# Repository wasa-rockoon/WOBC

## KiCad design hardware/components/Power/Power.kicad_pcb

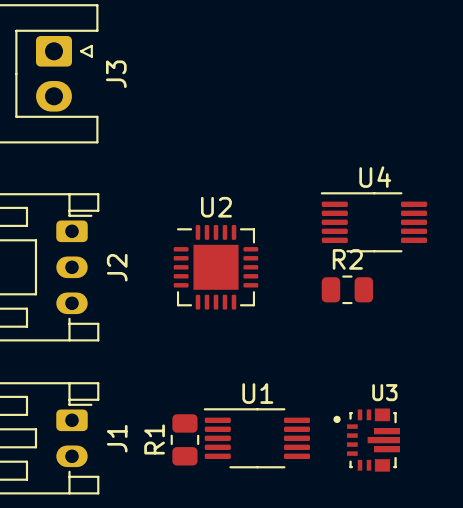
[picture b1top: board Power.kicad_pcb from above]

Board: 2 copper layers, 10 parts (1 on the bottom side), 11 nets, no tracks yet.

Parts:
BT1: Battery_Cell; BatteryHolder_Keystone_3002_1x2032
J1: LiPo; JST_PH_S2B-PH-K_1x02_P2.00mm_Horizontal
J2: Temp&Heater; JST_PH_S3B-PH-K_1x03_P2.00mm_Horizontal
J3: Battery; JST_XH_S2B-XH-A_1x02_P2.50mm_Horizontal
R1, R2: 50mΩ; R_0805_2012Metric
U1, U4: INA226; VSSOP-10_3x3mm_P0.5mm
U2: MCP73871-1CC; QFN-20-1EP_4x4mm_P0.5mm_EP2.5x2.5mm
U3: TPS63070RNMR; VREG_TPS63070RNMR

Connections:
GND: BT1.2 (-), J1.2, J2.3, J3.2, U1.7 (GND), U2.10 (V_{SS}), U2.11 (V_{SS}), U2.21 (V_{SS}), U4.7 (GND)
I2C_SCL: U1.5 (SCL), U4.5 (SCL)
I2C_SDA: U1.4 (SDA), U4.4 (SDA)
unnamed: U2.1 (OUT), U2.20 (OUT)
unnamed: J2.2, U2.5 (THERM)
unnamed: U2.18 (IN), U2.19 (IN)
unnamed: R1.1, U2.14 (V_{BAT}), U2.15 (V_{BAT}), U2.16 (V_{BAT_SENSE}), U4.6 (VS), U4.9 (Vin-)
unnamed: R1.2, U4.8 (Vbus), U4.10 (Vin+)
VBUS: U2.2 (VPCC), U2.3 (SEL)
VDD: R2.2, U1.9 (Vin-)
VDD_BUS: R2.1, U1.6 (VS), U1.8 (Vbus), U1.10 (Vin+)

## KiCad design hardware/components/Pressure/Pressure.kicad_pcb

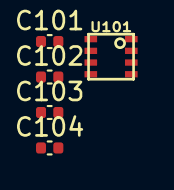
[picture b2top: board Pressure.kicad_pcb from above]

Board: 2 copper layers, 5 parts (0 on the bottom side), 2 nets, no tracks yet.

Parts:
C101, C104: 10μF; C_0402_1005Metric
C102, C103: 100nF; C_0402_1005Metric
U101: BME280

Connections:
3V3: C101.1, C102.1, C103.1, C104.1, U101.2 (CSB), U101.6 (VDDIO), U101.8 (VDD)
GND: C101.2, C102.2, C103.2, C104.2, U101.1 (GND), U101.5 (SDO), U101.7 (GND)

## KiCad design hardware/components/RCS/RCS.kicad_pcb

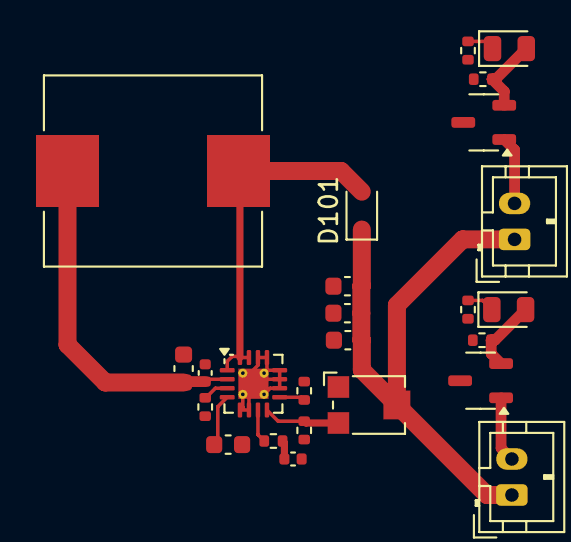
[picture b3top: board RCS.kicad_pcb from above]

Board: 2 copper layers, 25 parts (0 on the bottom side), 16 nets.

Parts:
C101: 47nF; C_0603_1608Metric
C102: 10uF; C_0603_1608Metric
C103, C104: 0.1uF; C_0402_1005Metric
C105, C106, C107: 4.7uF; C_0603_1608Metric
D101: D; D_SOD-323
D102, D103: Valve; D_0805_2012Metric
J101, J102: Conn_01x02; JST_PH_B2B-PH-K_1x02_P2.00mm_Vertical
L101: 10uH; L_Chilisin_BMRF00101040
Q101, Q102: NMOS; SOT-23-3
R101, R102, R105, R106: 100k; R_0402_1005Metric
R103: 2.2k; R_0402_1005Metric
R104, R107, R108: 1k; R_0402_1005Metric
RV101: 20k; Potentiometer_Bourns_TC33X_Vertical
U101: WQFN-16-1EP_3x3mm_P0.5mm_EP1.68x1.68mm_ThermalVias

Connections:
/RCS_EN: R101.1, U101.3 (EN)
/RCS_VIN: C102.1, C104.1, L101.1, U101.2 (VIN)
/valve1: D102.2 (A), Q101.2 (G), R105.1
/valve2: D103.2 (A), Q102.2 (G), R106.1
GND: C101.2, C102.2, C103.2, C104.2, C105.2, C106.2, C107.2, Q101.3 (S), Q102.3 (S), R101.2, R102.2, R104.2, R105.2, R106.2, R107.2, R108.2, U101.5 (SYNC), U101.6 (AGND), U101.10 (NC), U101.11 (PGND), U101.12 (PGND), U101.13 (PGND), U101.14 (NC), U101.17 (EP)
unnamed: C103.1, R103.2
unnamed: D101.2 (A), L101.2, U101.1 (SW), U101.15 (SW), U101.16 (SW)
unnamed: C105.1, C106.1, C107.1, D101.1 (K), J101.1, J102.1, RV101.2
unnamed: D102.1 (K), R107.1
unnamed: D103.1 (K), R108.1
unnamed: J101.2, Q101.1 (D)
unnamed: J102.2, Q102.1 (D)
unnamed: R103.1, U101.7 (COMP)
unnamed: R104.1, RV101.3, U101.8 (FB)
unnamed: R102.1, U101.9 (FREQ)
unnamed: C101.1, U101.4 (SS)

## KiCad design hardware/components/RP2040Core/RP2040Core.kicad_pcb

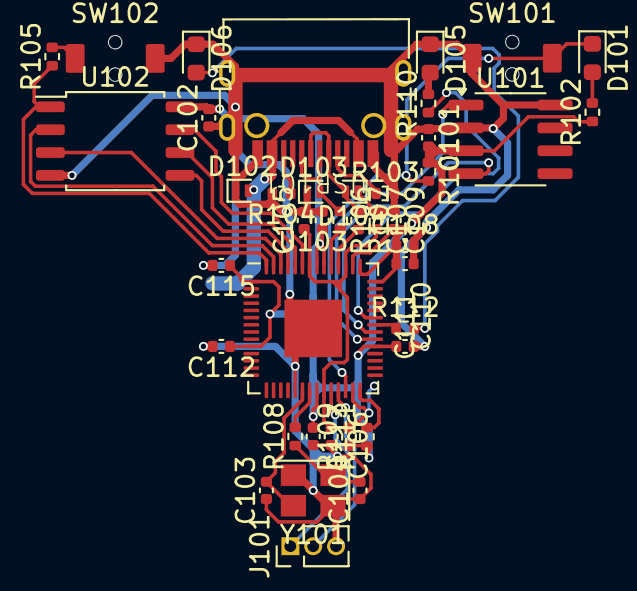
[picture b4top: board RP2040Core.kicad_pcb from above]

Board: 2 copper layers, 41 parts (0 on the bottom side), 32 nets.

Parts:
C101, C102, C105, C106, C108, C110, C111, C112, C113, C114, C115: 100nF; C_0402_1005Metric
C103, C104: 27pF; C_0402_1005Metric
C107, C109: 1uF; C_0402_1005Metric
D101: RESET; LED_0603_1608Metric
D102, D103, D104: 5V; D_SOD-882
D105: STAT; LED_0603_1608Metric
D106: ERROR; LED_0603_1608Metric
J101: DEBUG; PinHeader_1x03_P1.27mm_Vertical
R101, R109, R111: 10k; R_0402_1005Metric
R102, R105, R108, R110, R112: 1k; R_0402_1005Metric
R103, R104: 5.1k; R_0402_1005Metric
R106, R107: 22.4; R_0402_1005Metric
SW101: RESET_sw; TVAF06-A020B-R
SW102: BOOT0; TVAF06-A020B-R
U101: SN65HVD230; SOIC-8_3.9x4.9mm_P1.27mm
U102: W25Q128JVS; SOIC-8_5.23x5.23mm_P1.27mm
U103: RP2040; QFN-56-1EP_7x7mm_P0.4mm_EP3.2x3.2mm
USB101: USB_C_Receptacle_USB2.0; USB_C_TYPEC-301S-ACP16X7
Y101: Crystal_GND24; Crystal_SMD_3225-4Pin_3.2x2.5mm

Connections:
/CAN_RX: U101.4 (R), U103.35 (GPIO23)
/CAN_TX: U101.1 (D), U103.34 (GPIO22)
/I2C_SCL: R111.2, U103.28 (GPIO17)
/I2C_SDA: R109.2, U103.27 (GPIO16)
/USB_D+: D103.2 (A2), R106.1, USB101.A6 (D+), USB101.B6 (D+)
/USB_D-: D104.2 (A2), R107.1, USB101.A7 (D-), USB101.B7 (D-)
GND: C101.1, C102.1, C103.1, C104.1, C105.2, C106.2, C107.1, C108.2, C109.1, C110.2, C111.2, C112.2, C113.2, C114.2, C115.2, D102.1 (A1), D103.1 (A1), D104.1 (A1), D105.1 (K), D106.1 (K), J101.3, R103.2, R104.2, SW101.2, SW102.1, U101.2 (GND), U101.8 (Rs), U102.4 (GND), U103.19 (TESTEN), U103.57 (GND), USB101.A1 (GND), USB101.A12 (GND), USB101.B1 (GND), USB101.B12 (GND), USB101.S1 (SHIELD), Y101.2, Y101.4
unnamed: C104.2, R108.1, Y101.1
unnamed: D101.2 (A), R102.2
unnamed: D105.2 (A), R110.2
unnamed: D106.2 (A), R112.2
unnamed: J101.1, U103.24 (SWCLK)
unnamed: J101.2, U103.25 (SWD)
unnamed: R105.2, SW102.2
unnamed: U102.6 (CLK), U103.52 (QSPI_SCLK)
unnamed: U102.5 (DI(IO0)), U103.53 (QSPI_SD0)
unnamed: U102.2 (DO(IO1)), U103.55 (QSPI_SD1)
unnamed: U102.3 (IO2), U103.54 (QSPI_SD2)
unnamed: U102.7 (IO3), U103.51 (QSPI_SD3)
unnamed: R105.1, U102.1 (~CS), U103.56 (QSPI_SS)
unnamed: R112.1, U103.36 (GPIO24)
unnamed: R110.1, U103.37 (GPIO25)
unnamed: R107.2, U103.46 (USB_DM)
unnamed: R106.2, U103.47 (USB_DP)
unnamed: C105.1, C106.1, C107.2, U103.23 (DVDD), U103.45 (VREG_VOUT), U103.50 (DVDD)
unnamed: C103.2, U103.20 (XIN), Y101.3
unnamed: R108.2, U103.21 (XOUT)
unnamed: R103.1, USB101.A5 (CC1)
unnamed: R104.1, USB101.B5 (CC2)
RESET: D101.1 (K), R101.2, SW101.1, U103.26 (RUN)
VBUS: D102.2 (A2), USB101.A4 (VBUS), USB101.A9 (VBUS), USB101.B4 (VBUS), USB101.B9 (VBUS)
VDD: C101.2, C102.2, C108.1, C109.2, C110.1, C111.1, C112.1, C113.1, C114.1, C115.1, R101.1, R102.1, R109.1, R111.1, U101.3 (VCC), U102.8 (VCC), U103.1 (IOVDD), U103.10 (IOVDD), U103.22 (IOVDD), U103.33 (IOVDD), U103.42 (IOVDD), U103.43 (ADC_AVDD), U103.44 (VREG_IN), U103.48 (USB_VDD), U103.49 (IOVDD)

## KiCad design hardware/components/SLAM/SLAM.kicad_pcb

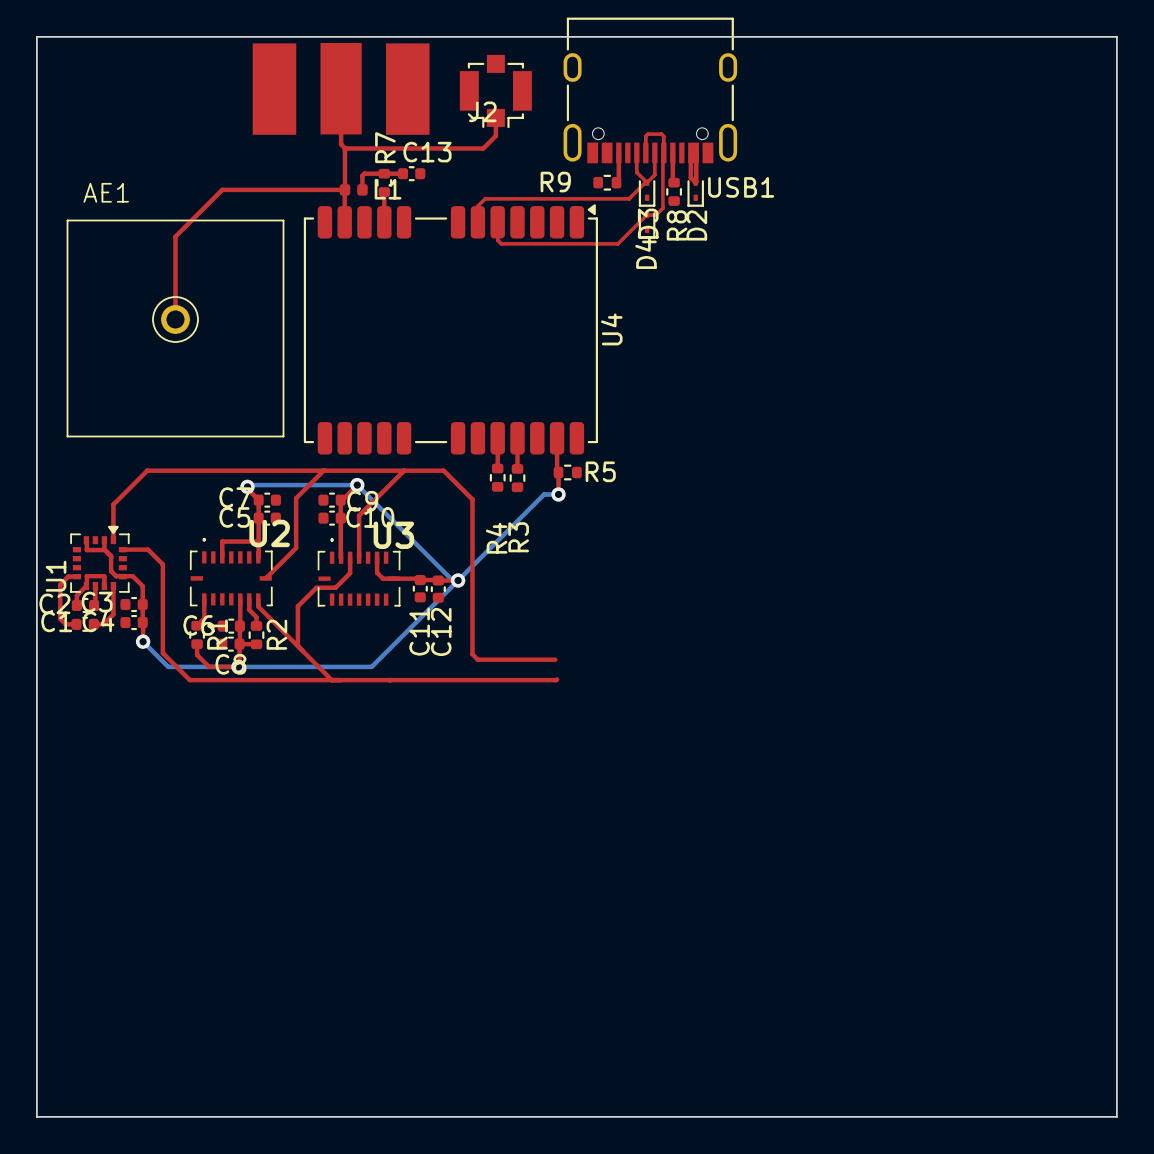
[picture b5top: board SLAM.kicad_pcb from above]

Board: 2 copper layers, 60.0 x 60.0 mm, 33 parts (0 on the bottom side), 19 nets.

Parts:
AE1: Antenna; GNSS_Antenna_1212
C1: 0.22μF; C_0402_1005Metric
C2: 4.7μF; C_0402_1005Metric
C3, C5, C6, C10, C11, C13: 100nF; C_0402_1005Metric
C4, C7, C8, C9, C12: 10μF; C_0402_1005Metric
D2, D3, D4: 5V; D_SOD-923
J1: SMA; SMA_aki
J2: U.FL; U.FL_Molex_MCRF_73412-0110_Vertical
L1: 27nH, 300mA; L_0402_1005Metric
R1, R2: 4.7K; R_0402_1005Metric
R3, R4: 33; R_0402_1005Metric
R5: 100K; R_0402_1005Metric
R7: 10; R_0402_1005Metric
R8, R9: 22k; R_0402_1005Metric
U1: LGA-16_3x3mm_P0.5mm
U2: BMI088
U3: BMI088
U4: NEO-M9N; ublox_NEO
USB1: USB_C_Receptacle_USB2.0; USB_C_Receptacle_XKB_U262-16XN-4BVC11

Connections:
3V3: C3.1, C4.1, C5.1, C6.1, C7.1, C8.1, C9.1, C10.1, C11.1, C12.1, R1.2, R2.2, R5.1, U1.2 (VDD), U1.4 (S1), U1.13 (VDDIO), U2.3 (VDD), U2.7 (PS), U2.11 (VDDIO), U3.2 (CSB), U3.6 (VDDIO), U3.8 (VDD), U4.23 (VCC)
/USB_D+: D3.2 (A2), U4.6 (USB_DP), USB1.A6 (D+), USB1.B6 (D+)
/USB_D-: D4.2 (A2), U4.5 (USB_DM), USB1.A7 (D-), USB1.B7 (D-)
AD0: R1.1, U2.15 (SDO1)
AD1: R2.1, U2.10 (SDO2)
GND: C2.2, C3.2, C4.2, C5.2, C6.2, C7.2, C8.2, C9.2, C10.2, C11.2, C12.2, C13.2, D2.1 (A1), D3.1 (A1), D4.1 (A1), J1.2 (Ext), J2.2 (Ext), R5.2, R8.2, R9.2, U1.9 (GND), U1.11 (GND), U2.4 (GNDA), U2.6 (GNDIO), U3.1 (GND), U3.5 (SDO), U3.7 (GND), U4.10 (GND), U4.12 (GND), U4.13 (GND), U4.24 (GND), USB1.A1 (GND), USB1.A12 (GND), USB1.B1 (GND), USB1.B12 (GND), USB1.S1 (SHIELD)
GPS_ANT1: AE1.1 (A), J1.1 (In), J2.1 (In), L1.1, U4.11 (RF_IN)
unnamed: C13.1, L1.2, R7.2
unnamed: D2.2 (A2), USB1.A4 (VBUS), USB1.A9 (VBUS), USB1.B4 (VBUS), USB1.B9 (VBUS)
unnamed: C2.1, U1.10 (C1)
unnamed: C1.1, U1.12 (SETC)
unnamed: C1.2, U1.8 (STEP)
unnamed: R3.1, U4.21 (RXD/SPI_MOSI)
unnamed: R4.1, U4.20 (TXD/SPI_MISO)
unnamed: R8.1, USB1.A5 (CC1)
unnamed: R9.1, USB1.B5 (CC2)
SCL: U1.1 (SCL), U2.8 (SCL/SCK), U3.4 (SCK)
SDA: U1.16 (SDA), U2.9 (SDA/SDI), U3.3 (SDI)
VCC_RF: R7.1, U4.9 (VCC_RF)

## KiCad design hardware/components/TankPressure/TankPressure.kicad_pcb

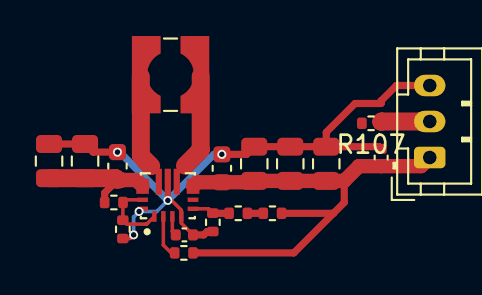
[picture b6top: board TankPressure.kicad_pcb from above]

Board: 2 copper layers, 19 parts (0 on the bottom side), 11 nets.

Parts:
C101, C102, C106, C107, C108: 22uF; C_0805_2012Metric
C103, C105: 10uF; C_0603_1608Metric
C104, C109: 100nF; C_0402_1005Metric
J101: Conn_01x03; JST_PH_B3B-PH-K_1x03_P2.00mm_Vertical
L101: 1.5uH; L_Wuerth_WE-TPC-3816
R101, R104: 10k; R_0402_1005Metric
R102: 330k; R_0402_1005Metric
R103: 100k; R_0402_1005Metric
R105, R107: 1k; R_0402_1005Metric
R106: 51k; R_0402_1005Metric
U101: TPS63070RNMR; VREG_TPS63070RNMR

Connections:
GND: C101.2, C102.2, C103.2, C104.2, C105.2, C106.2, C107.2, C108.2, C109.2, J101.3, R102.2, R104.1, U101.4 (GND), U101.10 (PGND), U101.15 (VSEL)
unnamed: C105.1, C106.1, C107.1, C108.1, C109.1, J101.1, R103.1, R106.2, U101.7_8 (VOUT)
unnamed: J101.2, R107.1
unnamed: R105.2, R106.1
unnamed: R101.1, R102.1, U101.1 (PS/SYNC), U101.14 (EN)
unnamed: R104.2, R105.1, U101.5 (FB)
unnamed: L101.1, U101.11 (L1)
unnamed: L101.2, U101.9 (L2)
unnamed: R103.2, U101.2 (PG)
unnamed: C104.1, U101.3 (VAUX)
VDD: C101.1, C102.1, C103.1, R101.2, U101.12_13 (VIN)

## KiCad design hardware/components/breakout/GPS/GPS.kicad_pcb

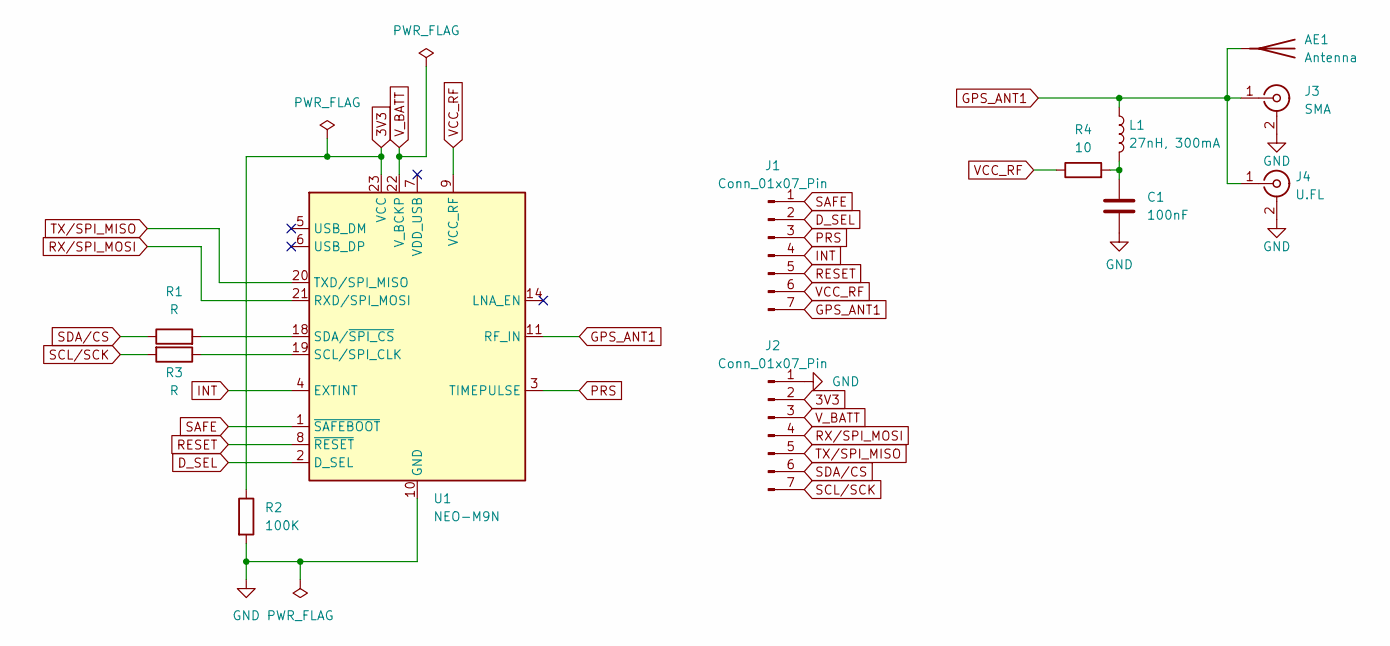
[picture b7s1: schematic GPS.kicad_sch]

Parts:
AE1: Antenna; GNSS_Antenna_1212
C1: 100nF; C_0402_1005Metric
J1, J2: Conn_01x07_Pin; PinHeader_1x07_P2.54mm_Vertical
J3: SMA; SMA_Amphenol_132289_EdgeMount
J4: U.FL; U.FL_Molex_MCRF_73412-0110_Vertical
L1: 27nH, 300mA; L_0402_1005Metric
R1, R3: R; R_0402_1005Metric
R2: 100K; R_0402_1005Metric
R4: 10; R_0402_1005Metric
U1: NEO-M9N; ublox_NEO

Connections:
3V3: J2.2, R2.1, U1.23 (VCC)
D_SEL: J1.2, U1.2 (D_SEL)
GND: C1.2, J2.1, J3.2 (Ext), J4.2 (Ext), R2.2, U1.10 (GND), U1.12 (GND), U1.13 (GND), U1.24 (GND)
GPS_ANT1: AE1.1 (A), J1.7, J3.1 (In), J4.1 (In), L1.1, U1.11 (RF_IN)
INT: J1.4, U1.4 (EXTINT)
unnamed: C1.1, L1.2, R4.2
unnamed: R3.1, U1.19 (SCL/SPI_CLK)
unnamed: R1.2, U1.18 (SDA/~SPI_CS)
PRS: J1.3, U1.3 (TIMEPULSE)
RESET: J1.5, U1.8 (~RESET)
RX/SPI_MOSI: J2.4, U1.21 (RXD/SPI_MOSI)
SAFE: J1.1, U1.1 (~SAFEBOOT)
SCL/SCK: J2.7, R3.2
SDA/CS: J2.6, R1.1
TX/SPI_MISO: J2.5, U1.20 (TXD/SPI_MISO)
VCC_RF: J1.6, R4.1, U1.9 (VCC_RF)
V_BATT: J2.3, U1.22 (V_BCKP)

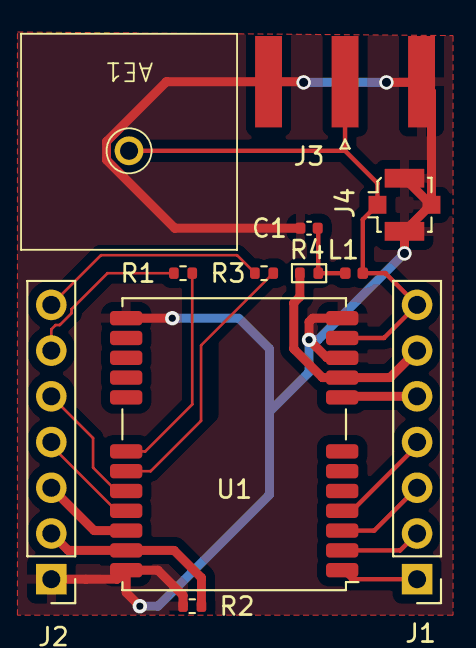
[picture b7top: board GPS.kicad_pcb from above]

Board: 2 copper layers, 12 parts (0 on the bottom side), 17 nets.
